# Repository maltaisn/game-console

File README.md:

# Handheld game console

A small six-button handheld game console with a bootloader and games stored in external flash memory.
A complete solution was created to create, simulate, compile and upload apps for the device.

There are currently 2 games written for the console:

- [Tetris](sw/app/tetris)
- [Tile World](sw/app/tworld)

## Specifications

- Display: 1.5" OLED 128x128, 4-bit gray.
- MCU: ATmega3208 @ 10 MHz, 4 kB RAM, 32 kB ROM (bootloader uses 8.25 kB).
- Memory: 4 kB EEPROM (up to 64 kB), 1 MB flash (up to 8 MB).
- Physical: 40 mm x 71 mm x 15.4 mm, 60 g.
- Battery: 850 mAh Li-Po, 5-20h active, several months standby, USB micro B charging.

### Hardware

- MCU: ATmega3208, compatible with ATmega4808, AVR128DA28, AVR64DA28, AVR32DA28 (none tested).
- EEPROM: FT25C32A, 4 kB (compatible with same series devices)
- Flash: AT25SF081B, 1 MB (compatible with 25-series flash devices)
- Display: EastRising ER-OLED015-3 (SSD1327 display controller, 15V VCC)

## Tools and building

Everything was built and tested on Linux only (Ubuntu 20.04).
The PCB was made in KiCAD 6 and the enclosure was made in FreeCAD 0.19.
Building and using the software requires the following tools and libraries:

- AVR GCC >= 5.4.0 (7.3.0 used)
- GCC >= 9
- Python >= 3.7
- freeglut, pulseaudio, libpng

## Architecture

The architecture of the software is described in details in [`sw/README.md`](sw/README.md).

## Project structure

- `hw`: PCB and enclosure
- `sw`: all software SDK including programming utility and all apps.
- `docs`: documentation source files

## License

All code is licensed under Apache License 2.0 and all assets are licensed under
Creative Commons v4.0, unless otherwise indicated.
Bitmap fonts were taken from the [u8g2](https://github.com/olikraus/u8g2/wiki/fntlistall) 
project and are not my work. Credits to my brother for making the game music.

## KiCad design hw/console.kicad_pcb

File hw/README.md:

# Game console hardware

## PCB

The PCB was designed in KiCAD 6.
Two revisions were made, but only the first revision was manufactured
since it was already working with minor changes.

### Revisions

#### Revision 2021A

- Initial revision.

#### Revision 2022A

- Added pull downs on the H-bridge.
- Removed power monitor (was originally meant to monitor shut off and alert the MCU to do last 
    minute operations, but there isn't anywhere near enough on-board capacity to have time to do so).
- Removed low power reset monitor on the MCU, it caused reset when disconnecting
  the USB cable due to momentary drop on 2.8V power rail (not properly decoupled, battery has protection anyway).
- Changed the battery connector which was too small.

Other notable changes that should be made:

- Battery discharge current reading at ADC to allow better SoC estimation.
- Attempt to reduce high pitch noise (related to either display or 15V boost, 
    may be due to ceramic caps oscillating).
- Increase clearance around buttons for better mechanical integration, or change buttons altogether.
- Remove unused H-bridge to drive speaker (only one side used). Replace bridge pull-downs with pull-ups.
- Replace the debug port with an integrated USB to UART chip.

## Enclosure

The enclosure was designed in FreeCAD and 3D printed in black MJF Nylon.
The design is fine considering this was my first experience with 3D modeling
and considering that it wasn't planned for carefully at the time of designing the
PCB. The button design could have been better, they sometimes get stuck and
don't click, but this is usually not an issue.

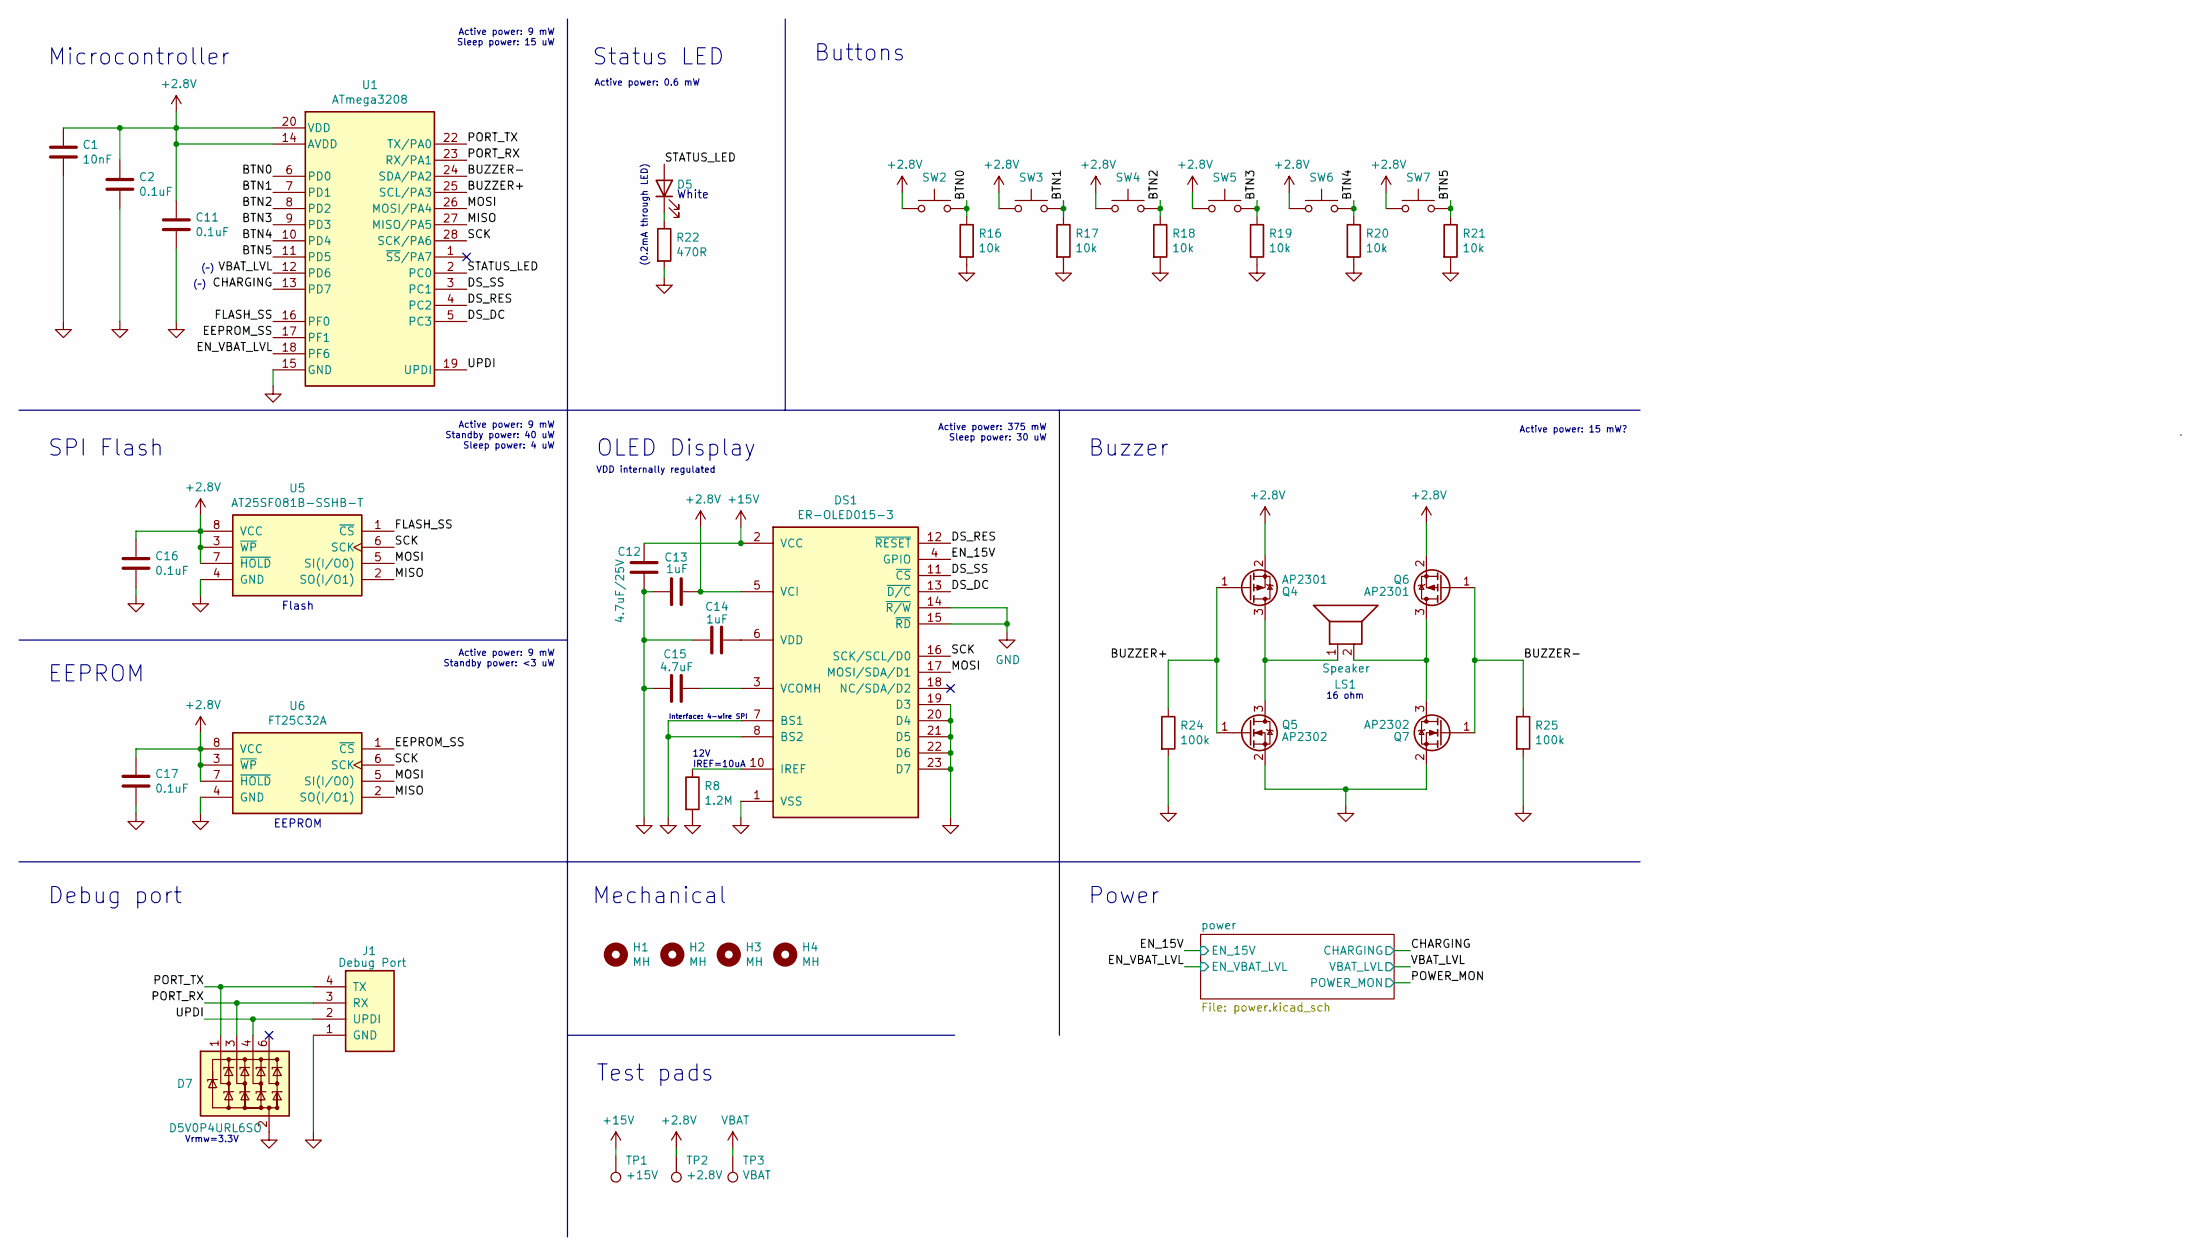
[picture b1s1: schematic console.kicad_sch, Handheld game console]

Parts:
C1: 10nF; C_0603_1608Metric
C2, C11, C16, C17: 0.1uF; C_0603_1608Metric
C12: 4.7uF/25V; C_0603_1608Metric
C13, C14: 1uF; C_0603_1608Metric
C15: 4.7uF; C_0603_1608Metric
D5: LED; D_0805_2012Metric
D7: D5V0P4URL6SO; SOT-23-6
DS1: ER-OLED015-3
H1, H2, H3, H4: MH; MountingHole_2.2mm_M2_ISO7380_Pad
J1: Debug Port; Debug_Port
LS1: Speaker
Q4, Q6: AP2301; SOT-23
Q5, Q7: AP2302; SOT-23
R8: 1.2M; R_0603_1608Metric
R16, R17, R18, R19, R20, R21: 10k; R_0603_1608Metric
R22: 470R; R_0603_1608Metric
R24, R25: 100k; R_0603_1608Metric
SW2, SW3, SW4, SW5, SW6, SW7: SW_Push; SW_SPST_TL3342
TP1: +15V; TestPoint_Pad_D2.0mm
TP2: +2.8V; TestPoint_Pad_D2.0mm
TP3: VBAT; TestPoint_Pad_D2.0mm
U1: ATmega3208; SSOP-28_5.3x10.2mm_P0.65mm
U5: AT25SF081B-SSHB-T; SOIC-8_3.9x4.9mm_P1.27mm
U6: FT25C32A; SO-8_3.9x4.9mm_P1.27mm

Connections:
+2V8: C1.1, C2.1, C11.1, C13.1, C16.1, C17.1, DS1.5 (VCI), Q4.2 (S), Q6.2 (S), SW2.1, SW3.1, SW4.1, SW5.1, SW6.1, SW7.1, TP2.1, U1.14 (AVDD), U1.20 (VDD), U5.3 (~WP), U5.7 (~HOLD), U5.8 (VCC), U6.3 (~WP), U6.7 (~HOLD), U6.8 (VCC); also elsewhere on the board
+15V: C12.1, DS1.2 (VCC), DS1.24 (VCC), TP1.1; also elsewhere on the board
/BTN0: R16.1, SW2.2, U1.6 (PD0)
/BTN1: R17.1, SW3.2, U1.7 (PD1)
/BTN2: R18.1, SW4.2, U1.8 (PD2)
/BTN3: R19.1, SW5.2, U1.9 (PD3)
/BTN4: R20.1, SW6.2, U1.10 (PD4)
/BTN5: R21.1, SW7.2, U1.11 (PD5)
/BUZZER+: Q4.1 (G), Q5.1 (G), R24.1, U1.25 (SCL/PA3)
/BUZZER-: Q6.1 (G), Q7.1 (G), R25.1, U1.24 (SDA/PA2)
/CHARGING: U1.13 (PD7); also elsewhere on the board
/DS_DC: DS1.13 (~D/C), U1.5 (PC3)
/DS_RES: DS1.12 (~RESET), U1.4 (PC2)
/DS_SS: DS1.11 (~CS), U1.3 (PC1)
/EEPROM_SS: U1.17 (PF1), U6.1 (~CS)
/EN_15V: DS1.4 (GPIO); also elsewhere on the board
/EN_VBAT_LVL: U1.18 (PF6); also elsewhere on the board
/FLASH_SS: U1.16 (PF0), U5.1 (~CS)
/MISO: U1.27 (MISO/PA5), U5.2 (SO(I/O1)), U6.2 (SO(I/O1))
/MOSI: DS1.17 (MOSI/SDA/D1), U1.26 (MOSI/PA4), U5.5 (SI(I/O0)), U6.5 (SI(I/O0))
/PORT_RX: D7.3 (K2), J1.3 (RX), U1.23 (RX/PA1)
/PORT_TX: D7.1 (K1), J1.4 (TX), U1.22 (TX/PA0)
/SCK: DS1.16 (SCK/SCL/D0), U1.28 (SCK/PA6), U5.6 (SCK), U6.6 (SCK)
/STATUS_LED: D5.2 (A), U1.2 (PC0)
/UPDI: D7.4 (K3), J1.2 (UPDI), U1.19 (UPDI)
/VBAT_LVL: U1.12 (PD6); also elsewhere on the board
GND: C1.2, C2.2, C11.2, C12.2, C13.2, C14.1, C15.1, C16.2, C17.2, D7.2 (VSS), DS1.1 (VSS), DS1.7 (BS1), DS1.8 (BS2), DS1.9 (VSS), DS1.14 (~R/W), DS1.15 (~RD), DS1.19 (D3), DS1.20 (D4), DS1.21 (D5), DS1.22 (D6), DS1.23 (D7), DS1.25 (VSS), J1.1 (GND), Q5.2 (S), Q7.2 (S), R8.2, R16.2, R17.2, R18.2, R19.2, R20.2, R21.2, R22.2, R24.2, R25.2, U1.15 (GND), U1.21 (GND), U5.4 (GND), U6.4 (GND); also elsewhere on the board
unnamed: C14.2, DS1.6 (VDD)
unnamed: C15.2, DS1.3 (VCOMH)
unnamed: D5.1 (K), R22.1
unnamed: DS1.10 (IREF), R8.1
unnamed: LS1.1, Q4.3 (D), Q5.3 (D)
unnamed: LS1.2, Q6.3 (D), Q7.3 (D)
VBAT: TP3.1; also elsewhere on the board

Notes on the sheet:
SPI Flash
Microcontroller
Debug port
16 ohm
Buttons
Interface: 4-wire SPI
Test pads
Flash
Power
Vrmw=3.3V
Active power: 375 mW Sleep power: 30 uW
(~)
White
Mechanical
IREF=10uA
EEPROM
OLED Display
Active power: 15 mW?
Active power: 9 mW Standby power: <3 uW
Buzzer
Active power: 9 mW Sleep power: 15 uW
Status LED
12V
VDD internally regulated
Active power: 0.6 mW
Active power: 9 mW Standby power: 40 uW Sleep power: 4 uW
(0.2mA through LED)

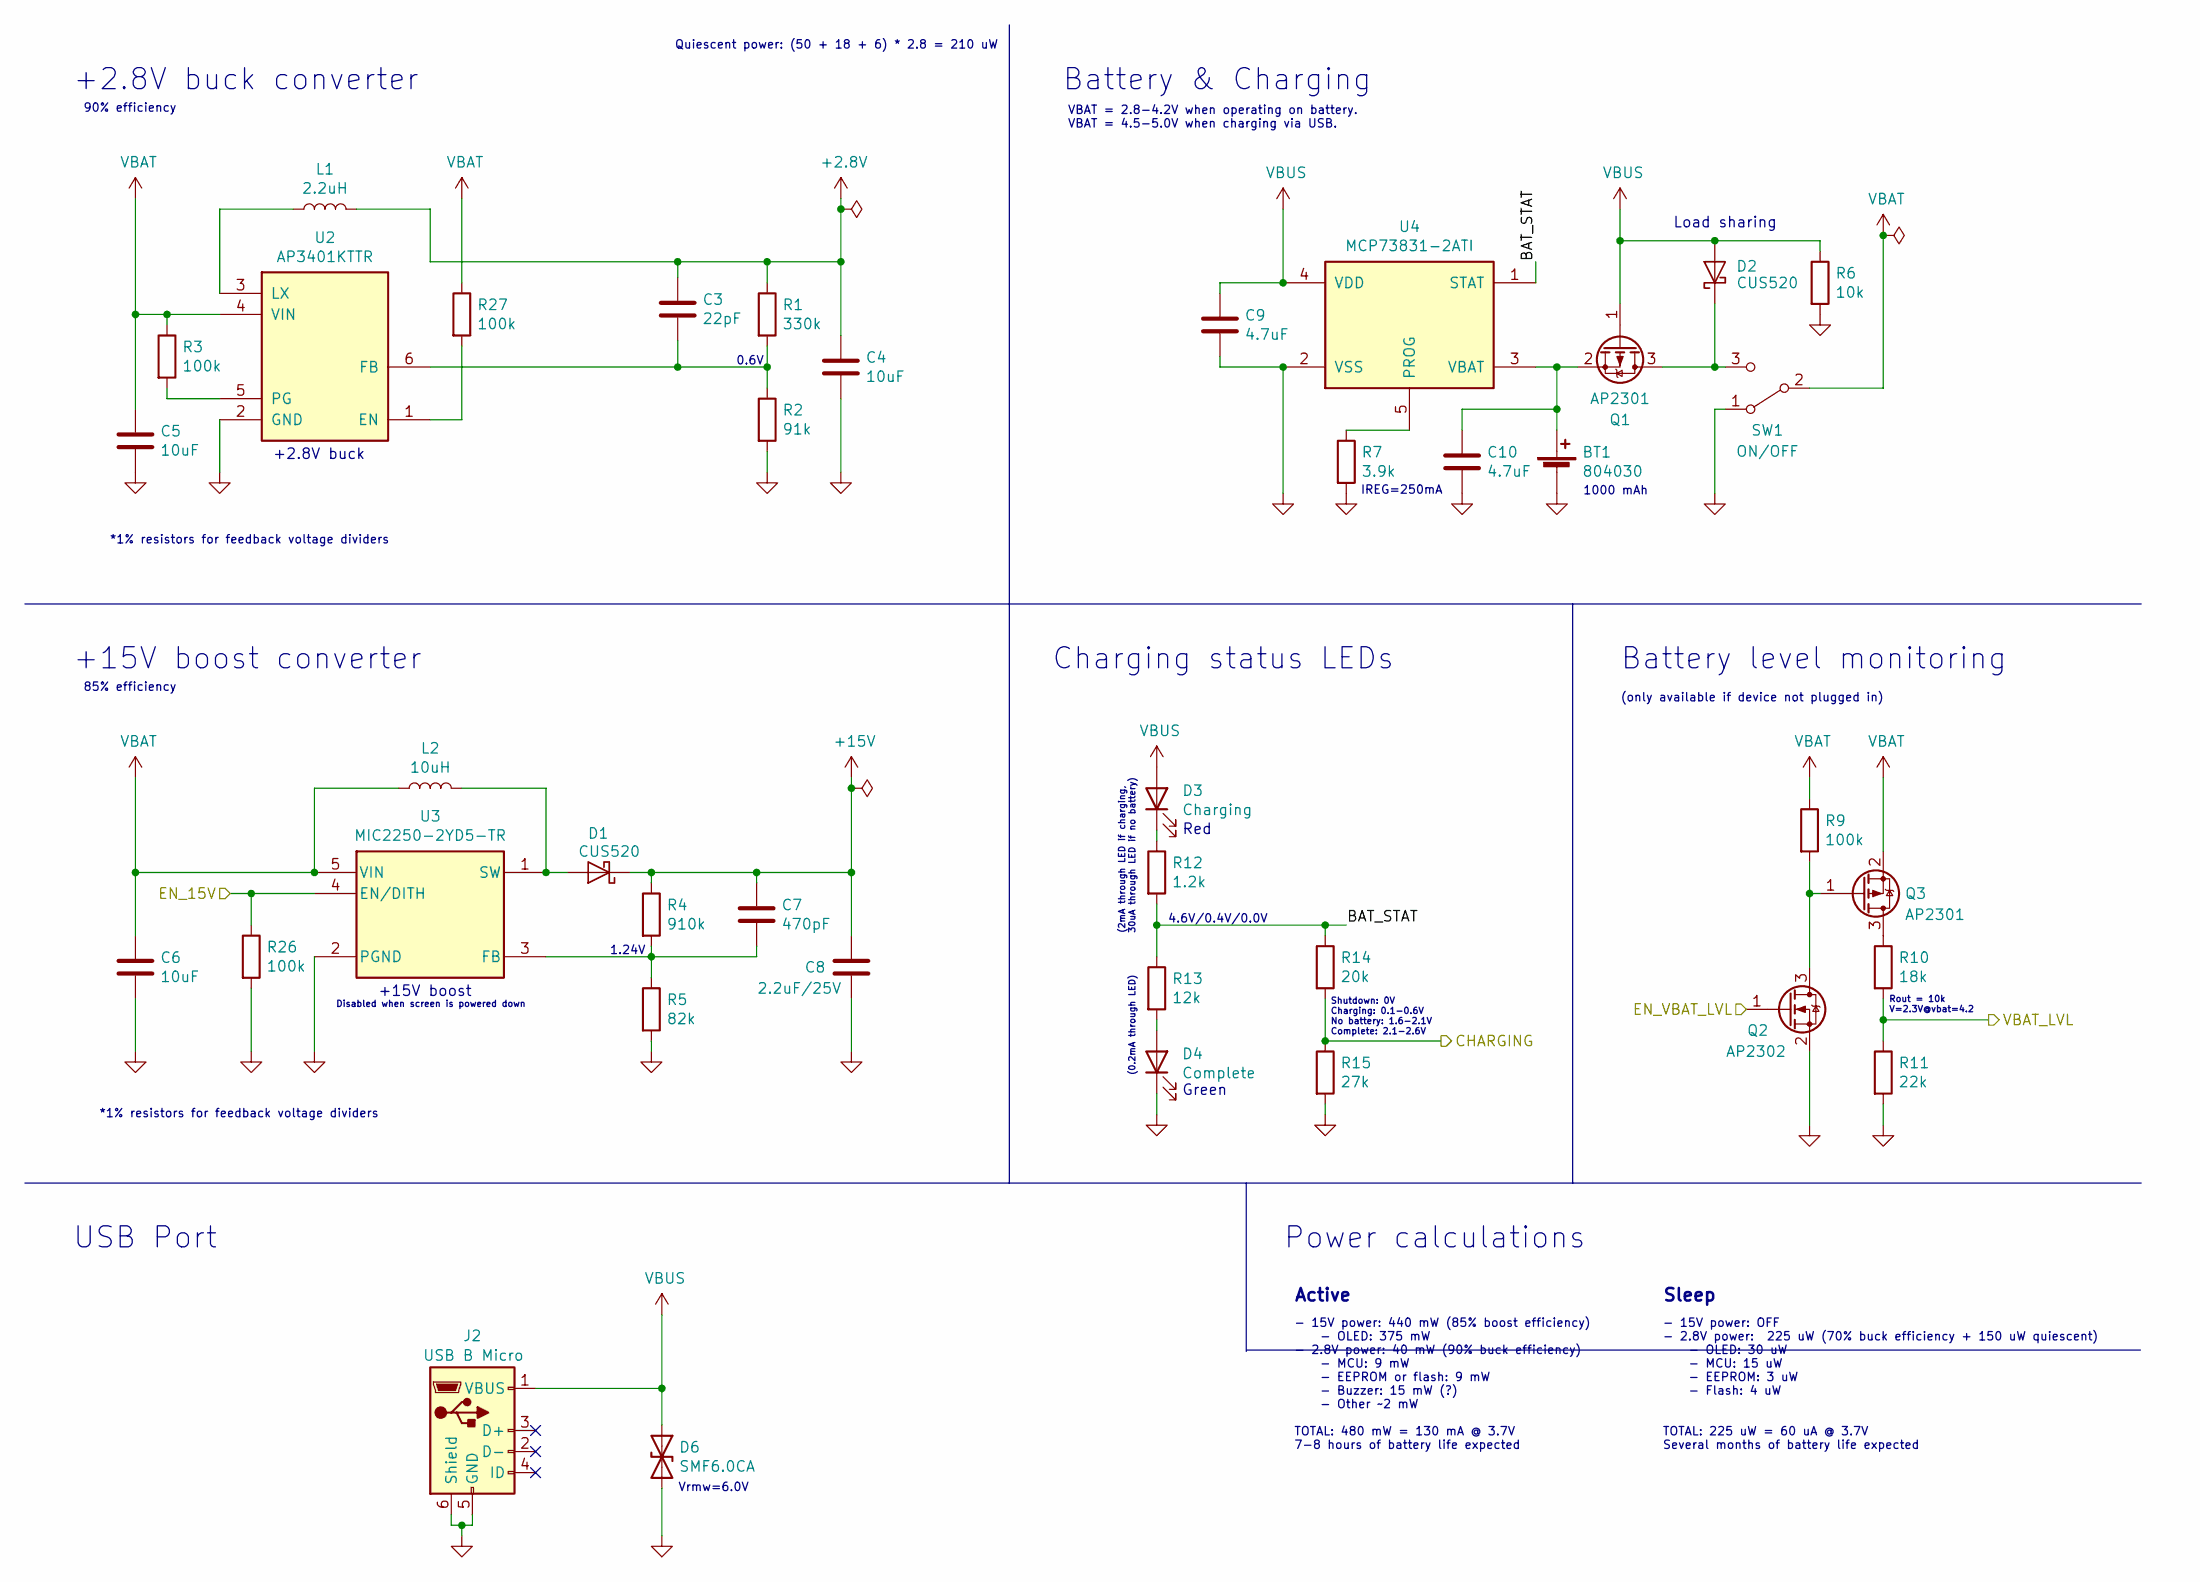
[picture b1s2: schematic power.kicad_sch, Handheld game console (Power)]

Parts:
BT1: 804030; Battery-804030
C3: 22pF; C_0603_1608Metric
C4, C5, C6: 10uF; C_0805_2012Metric
C7: 470pF; C_0603_1608Metric
C8: 2.2uF/25V; C_0603_1608Metric
C9, C10: 4.7uF; C_0603_1608Metric
D1, D2: CUS520; D_SOD-323_HandSoldering
D3: Charging; D_0805_2012Metric
D4: Complete; D_0805_2012Metric
D6: SMF6.0CA; D_SOD-123F
J2: USB B Micro; CUI_UJ2-MIBH-G-SMT-TR
L1: 2.2uH; L_1210_3225Metric
L2: 10uH; L_1210_3225Metric
Q1, Q3: AP2301; SOT-23
Q2: AP2302; SOT-23
R1: 330k; R_0603_1608Metric
R2: 91k; R_0603_1608Metric
R3, R9, R26, R27: 100k; R_0603_1608Metric
R4: 910k; R_0603_1608Metric
R5: 82k; R_0603_1608Metric
R6: 10k; R_0603_1608Metric
R7: 3.9k; R_0603_1608Metric
R10: 18k; R_0603_1608Metric
R11: 22k; R_0603_1608Metric
R12: 1.2k; R_0603_1608Metric
R13: 12k; R_0603_1608Metric
R14: 20k; R_0603_1608Metric
R15: 27k; R_0603_1608Metric
SW1: ON/OFF; 1825232-1
U2: AP3401KTTR; SOT-23-6
U3: MIC2250-2YD5-TR; SOT-23-5
U4: MCP73831-2ATI; SOT-23-5

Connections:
+2V8: C3.1, C4.1, L1.2, R1.1; also elsewhere on the board
+15V: C7.1, C8.1, D1.1 (C), R4.1; also elsewhere on the board
/CHARGING: R14.2, R15.1; also elsewhere on the board
/EN_15V: R26.1, U3.4 (EN/DITH); also elsewhere on the board
/EN_VBAT_LVL: Q2.1 (G); also elsewhere on the board
/VBAT_LVL: R10.2, R11.1; also elsewhere on the board
/power/BAT_STAT: R12.2, R13.1, R14.1, U4.1 (STAT)
GND: BT1.2 (-), C4.2, C5.2, C6.2, C8.2, C9.2, C10.2, D4.1 (K), D6.2 (A2), J2.5 (GND), J2.6 (Shield), Q2.2 (S), R2.2, R5.2, R6.2, R7.2, R11.2, R15.2, R26.2, SW1.1 (A), U2.2 (GND), U3.2 (PGND), U4.2 (VSS); also elsewhere on the board
unnamed: BT1.1 (+), C10.1, Q1.2 (S), U4.3 (VBAT)
unnamed: C3.2, R1.2, R2.1, U2.6 (FB)
unnamed: C7.2, R4.2, R5.1, U3.3 (FB)
unnamed: D1.2 (A), L2.2, U3.1 (SW)
unnamed: D2.1 (C), Q1.3 (D), SW1.3 (C)
unnamed: D3.1 (K), R12.1
unnamed: D4.2 (A), R13.2
unnamed: L1.1, U2.3 (LX)
unnamed: Q2.3 (D), Q3.1 (G), R9.2
unnamed: Q3.3 (D), R10.1
unnamed: R3.2, U2.5 (PG)
unnamed: R7.1, U4.5 (PROG)
unnamed: R27.2, U2.1 (EN)
VBAT: C5.1, C6.1, L2.1, Q3.2 (S), R3.1, R9.1, R27.1, SW1.2 (B), U2.4 (VIN), U3.5 (VIN); also elsewhere on the board
VBUS: C9.1, D2.2 (A), D3.2 (A), D6.1 (A1), J2.1 (VBUS), Q1.1 (G), R6.1, U4.4 (VDD)

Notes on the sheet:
(only available if device not plugged in)
85% efficiency
Red
Sleep
Power calculations
(0.2mA through LED)
Green
Battery & Charging
- 15V power: OFF - 2.8V power: 225 uW (70% buck efficiency + 150 uW quiescent) - OLED: 30 uW - MCU: 15 uW - EEPROM: 3 uW - Flash: 4 uW TOTAL: 225 uW = 60 uA @ 3.7V Several months of battery life expected
90% efficiency
1000 mAh
0.6V
Vrmw=6.0V
1.24V
*1% resistors for feedback voltage dividers
Battery level monitoring
- 15V power: 440 mW (85% boost efficiency) - OLED: 375 mW - 2.8V power: 40 mW (90% buck efficiency) - MCU: 9 mW - EEPROM or flash: 9 mW - Buzzer: 15 mW (?) - Other ~2 mW TOTAL: 480 mW = 130 mA @ 3.7V 7-8 hours of battery life expected
(2mA through LED if charging, 30uA through LED if no battery)
4.6V/0.4V/0.0V
+2.8V buck converter
VBAT = 2.8-4.2V when operating on battery. VBAT = 4.5-5.0V when charging via USB.
Shutdown: 0V Charging: 0.1-0.6V No battery: 1.6-2.1V Complete: 2.1-2.6V
+15V boost converter
Active
USB Port
Rout = 10k V=2.3V@vbat=4.2
Charging status LEDs
Load sharing
+15V boost
Disabled when screen is powered down
IREG=250mA
+2.8V buck
Quiescent power: (50 + 18 + 6) * 2.8 = 210 uW

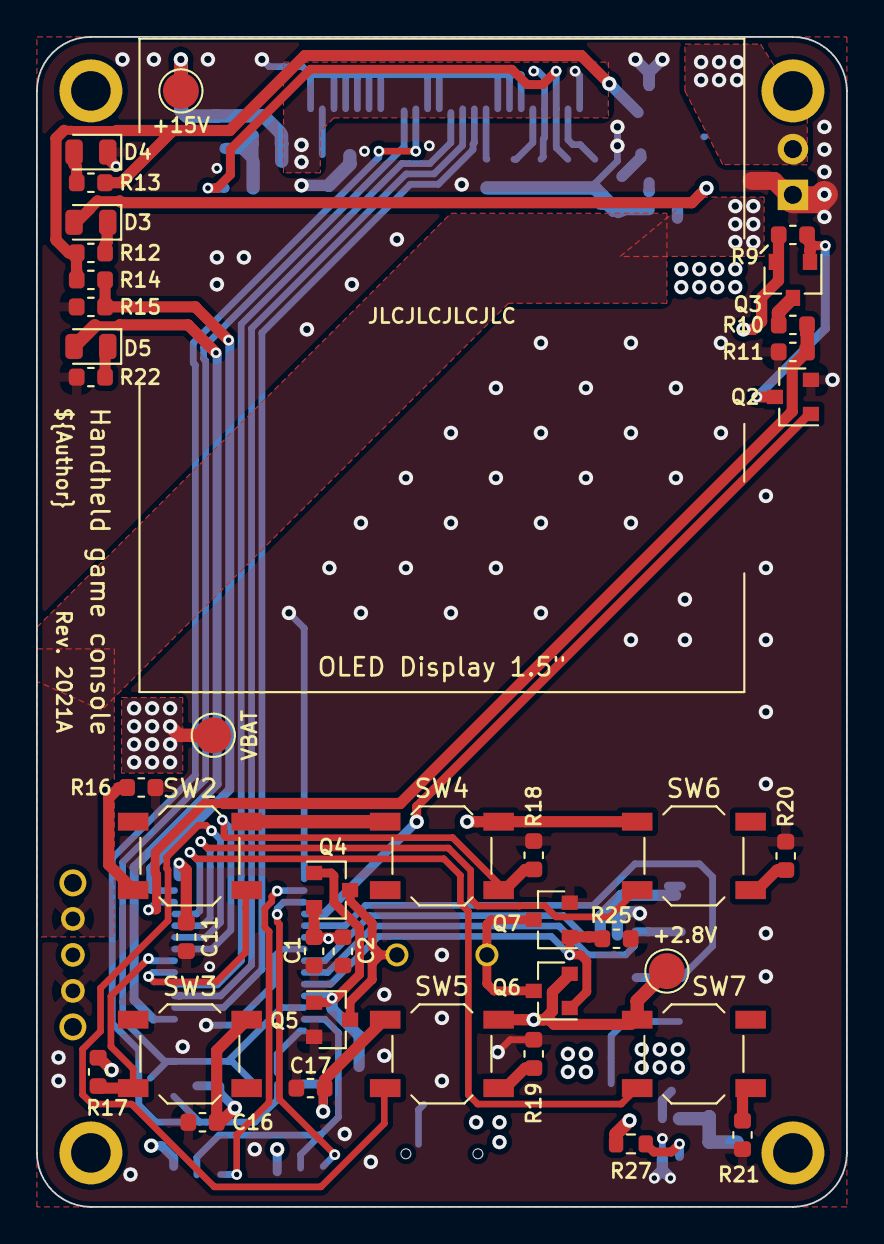
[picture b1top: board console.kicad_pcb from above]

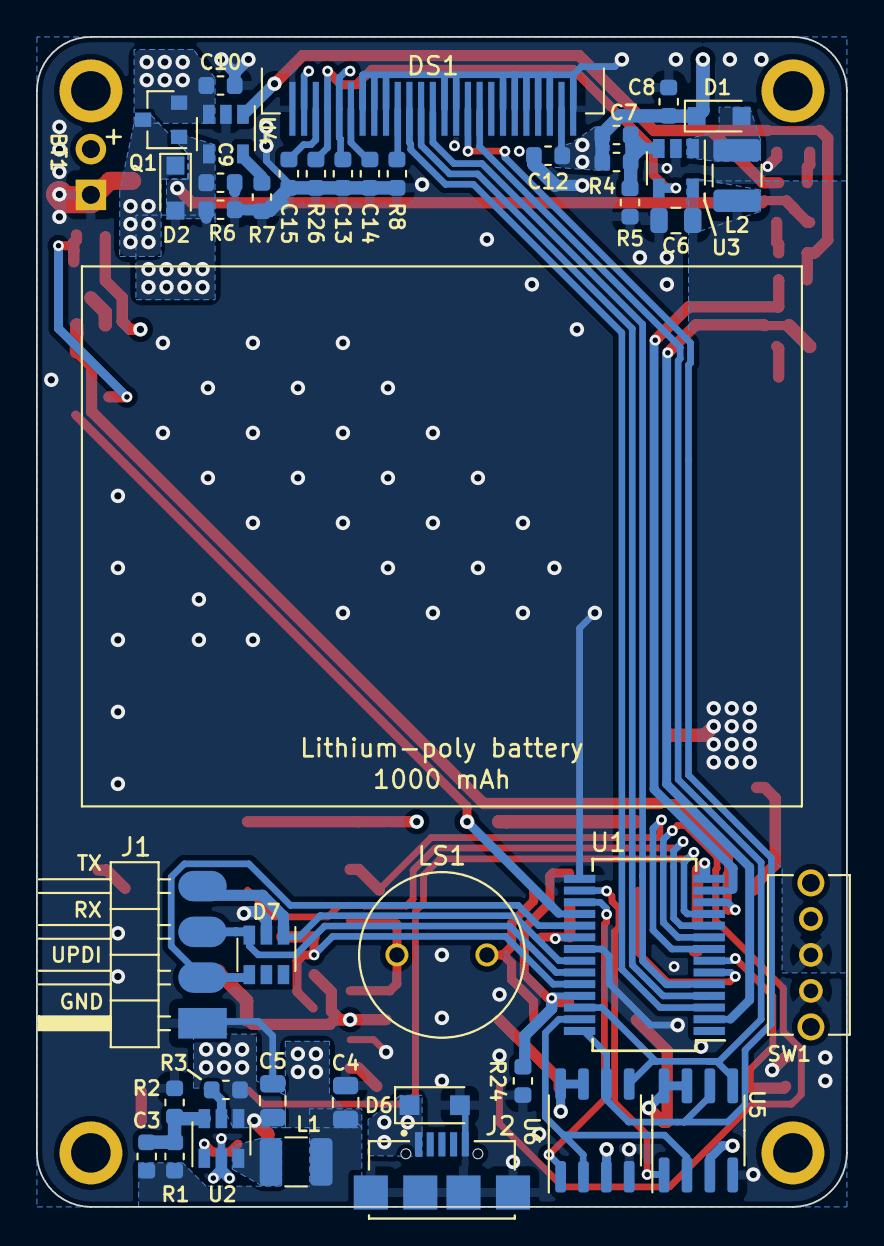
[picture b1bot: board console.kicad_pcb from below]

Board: 4 copper layers, 45.0 x 65.0 mm, 84 parts (40 on the bottom side), 49 nets.

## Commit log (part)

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2021-12-20 Initial commit: hardware
2021-12-22 License & readme
2021-12-22 Move system code to separate folder, power module optimizations
2021-12-22 Automatic battery sampling, battery level buffering, auto shutdown
2021-12-23 Remove option to have no RX/TX buffer
    Not viable!
2021-12-24 Add some const local variables, _WBS
2021-12-24 Add flash driver to gcprog
    Change link baud rate to 500k otherwise reading & writing to flash is painfully slow!
2021-12-27 Add defines for uint24_t
    Will serve later for mock simulator implementation
2021-12-28 Add sound support with 3 channels
    Note: having upload issue, not fully tested.
2021-12-30 Display driver, graphics draw functions, simulated display
    Note: not tested on hardware yet
2021-12-31 Implement graphics line routines, add font/image prototypes
2021-12-31 Performance improvements on graphics_draw_line
2022-01-01 Add text & font to graphics module
    - Fix data module in simulator
    - Add file error guards to eeprom/flash_load_file
2022-01-05 Add 1-bit & 4-bit images to graphics
2022-01-05 Remove .sim file, use two build directories instead
2022-01-06 Code improvements
    - Some const
    - static to indicate length of arrays/buffers
    - Finished implementing sleep
2022-01-06 Add sound generation utility
    Stripped down from buzzer midi project
2022-01-06 Use __builtin_add_overflow for portability
    Program size did not change on AVR target.
2022-01-07 Sleep scheduling and low battery UI
    - Fix glyph not using correct data when font in program memory.
    - Add sleep packet
    - Power down flash before sleep
    - Add built-in graphics font 3x5
    - Add define to disable comms
2022-01-08 Add dialog core module, bug fix
    - Fix graphics_image only drawing the first page due to wrongly placed early exit.
    - Fix font generator giving wrong encoded range info
2022-01-08 Remove unused ellipse/circle graphics prototypes
2022-01-08 Dialog improvements & bug fixes
    - Fix up arrow working from action button in dialog with no items
    - Allow custom result codes for built-in dialog actions.
    - Fix bottom of frame not drawn if title + no buttons
2022-01-10 Add guards to display buffer
    Poor man's valgrind
2022-01-10 Tetris: "how to play" dialog
    - Fix dialog dismiss result not using negative button result if unspecified
2022-01-10 Tetris: render preview pieces & held piece
    - Fix leaderboard dismiss starting game
    - Save options when positive button used
2022-01-10 Tetris: add last clear bonus info
2022-01-10 Add power sleep callbacks
2022-01-11 Tetris: implement leaderboard and high score
2022-01-14 Fix upload bug & many due firmware fixes
    Note: firmware functions hadn't been tested from this commit to 1874ff4a.
    - firmware:
    - Fix unified data interface not working for eeprom & mcu
    - Add protection against dirty resets
    - Set buzzer output high initially (seems to fix a rare reset glitch)
    - Change display driver to do continuous SPI transfers (supported after all, much faster)
2022-01-14 Fix sound corrupting display
    Due to sound track filling its buffer in an interrupt, while SPI transfer for display was in progress.
2022-01-14 Tetris: use primitives instead of images for tiles, flash header check
2022-01-15 Tetris: add music & title screen image
    - Preview volume level in options dialog
    - Add different leaderboard state if shown during game or in main menu.
    - Fix blinking LED on game over not stopped if new game started shortly after.
    - Fix outline for hold piece color constantly changing.
    - Fix leaderboard being written past its end if full.
    - Show version info in title screen.
2022-01-16 Tetris: fix input not ignored on wakeup
    input_get_state_immediate worked, but following input_get_state is debounced and delayed, so it indicated the button as released right after.
2022-01-16 Tetris: add delay between music changes
    - Fix line clear info color changing
2022-01-17 Add missing core assets for sysui
2022-01-17 Linearize grayscale levels on display
    Note: will have to check later which settings minimize power consumption.
2022-01-18 Power module fixes
    - Speaker causes voltage drop on vbus (?), causing failure to detect no battery condition (becomes unknown), so voltage range was widened a bit.
    - Fix enable battery voltage pin not set as output, which caused intermittent failure to read battery level (surprising it worked at all...)
    - Refactor ADC interrupt code a little, removed useless battery percent cache flag.
2022-01-23 Tetris: add sound effects
2022-01-23 Fix channel volume simulator implementation
2022-01-30 Fix cases where display buffer size created short last page
    - Make display_page_yend inclusive
    - Fix implementation issues with different last page height
    - Fix incorrect line spacing runtime check in graphics_set_font
    - Allow changing page height at runtime in simulator
    - Fix headless simulator not initialized in graphics_test
    From here the strategy when making new games is to allocate all leftover RAM to the display buffer, even if it results in weird page heights, like 37, a larger page height will always be faster.
2022-01-31 Add missing reference data for graphics tests
2022-01-31 Reduce branching and provide fast path for RLE sequence in mixed 4-bit image decoder
    For tiger128.png: 148 ms (77cyc/px) -> 134 ms (68cyc/px)
    Optimizing only the function with -O3 gives 121 ms but +270 bytes.
2022-01-31 Change indexing for raw images: implicit index
    - Raw image layout is predictable hence index is useless. Seeking to the first row is possible trivially, provided that the encoder state is reset on each row.
    - Few swap optimizations (a color always has high nibble = 0).
2022-02-05 Add linker script to optimize RAM usage
    - Add section to share RAM with display buffer, for temporary data (wouldn't have been a problem with a heap!).
    - Add script to better calculate section size (other methods have some shortcomings)
    - Put some static variables in noinit section (not much of an optimization, more self documentation actually)
    - Fix display state not reset on display reset.
2022-02-26 Tetris: bug fixes & improvements
    - Increase block constrast (some blocks were really hard too see on gc), and update title screen image accordingly
    - Add access to general options from pause dialog.
    core/sys bugs:
    - Fix sound_start and sound_stop not stoppping or
    starting notes on affected channels.
    - Fix buffer underflow in dialog text field if all blank.
2022-03-06 Tetris: increase tempo with level
2022-04-24 PCB: removed reset monitor
    Causes drop in power when USB is disconnected and not really necessary.
2022-05-23 System app
    - Add defines in dialog to disable features to lower code size.
    - Add define to use EEPROM in absolute mode (for bootloader and system app)
    - Fix include leaking system API in several places
    - Fix boot version not read correctly due to make lazy initialization
    - Remove all pthread uses, wasn't really needed.
2022-05-28 SPI device emulation and various fixes
    - Flash and EEPROM are not entirely in the core library, same code runs in simulation.
    - Add --sim mode to gcprog as a UART client to the simulator
    - Abstraction over external memory simulation functions.
    - Fix wrong load address for shared data section
    - Fix unable to read whole memory in raw access mode in gcprog
    - Fix broken test target with previous changes to Makefiles
2022-05-28 Update graphics image tests (remove horizontal region)
    - Fix image encoder not checking max dimensions
    - Add runtime check for image x bounds.
    - Fix color byte not reset on row boundary when encoding 1-bit raw images
    - Auto fix path when running standalone encode utilities.
2022-06-03 Several fixes: bootloader now working on hardware
    Bootloader:
    - Select last loaded app by default.
    - Prevent signature of some BOOTLOADER_NOINLINE functions changing due to constant propagation.
    - Remove lock on oscillator calibration registers preventing clock calibration, see errata.
    - Program fuses with the HEX file instead of manually.
    - Fix wrong protected write type used for enabling SPM.
2022-06-04 Include subsection usage in avr_size.py
2022-06-04 System app fixes
    - Fix battery voltage shown when not discharging.
    - Fix relative flash read used to read app name and author.
2022-06-12 Fix concurrency issue with simulated flash and eeprom.
2022-06-14 Documentation
2022-06-17 TWorld: level pack selection
    - Asset packer fixes:
    - Fix missing array when last packed object belongs in an array.
    - Fix missing array when consecutive objects form different arrays.
    - Fix underscore not allowed in group name.
2022-06-19 TWorld: utility functions
2022-06-22 TWorld: implement password use
2022-06-23 TWorld: fixes after first hardware test
    - Fix wrong frame delay comparison causing low FPS.
    - Fix missing cast in LZSS 2 bytes backref decoding.
    - Fix level pack rendering showing one extra pack when less than 4 packs.
    Core library:
    - Fix annoying clang-tidy warning asking to use lround in millis_to_ticks.
    - Add FPS monitor utility.
2022-06-24 TWorld: show time left with inventory, low time counter
    - Track time left instead of current time.
    - Hide inventory when pause dialog is shown.
    - Fix unlocked packs cleared by saving options.
2022-06-25 TWorld: show hint
    - Add separator game states for better maintainability.
    - Fix bottom navigation arrow wrong color if less items than can be shown in a single screen.
2022-06-26 TWorld: level music
    Reused same music controller as tetris, some features may be removed later.
2022-06-29 TWorld: main menu music
2022-06-29 TWorld: level fail dialog message
    - Add option for top margin in dialog module.
    - Small optimization in dialog_init.
    - Fix fading pattern appearing wrong with 16 colors only in main menu image
    - Add string builder in assets packer.
    - Distinguish between block and monster collision.
2022-07-01 TWorld: level tests, level pack unlocking
    - Add automatic level tests for all levels in all packs.
    - Unlock level packs if previous has a certain completion ratio.
    - Fix cloner copying actor index of parent to clone.
    - Fix misplaced return in teleport_actor.
    - Fix wrong THIN_WALL_DIR_TO mask.
    - Fix blob PRNG used for tests.
2022-07-01 Tworld: animated bottom tiles
2022-07-02 Bootloader & core library fixes
    - Fix CRC check failing when code size is multiple of page size.
    - Fix boot symbols filter not excluding some unwanted symbols.
    - Misc fixes to remove warnings on avr-gcc 12 (but avr-gcc 12 not working yet...)
    - Fix sleep countdown not working in simulator.
2022-07-03 TWorld: swimming, burned & drowned chip tiles
    - Fix wrong state delay on fail/complete.
2022-07-08 TWorld: bug fix
    - Fix diagonal input resolution not using last chip direction but sometimes forced direction.
    - More efficient tile macros, re-encoded static bottom tiles.
2022-07-09 TWorld: python implementation
2022-07-10 System app simulation bug fix
    - Fix structs not packed causing manual memory address calculation to be misaligned.
2022-07-22 TWorld: bug fixes
    - Fix type 1 collision not occuring when chip overrides force move
    - Fix unslide working in some cases on ice (and maybe teleporter)
    - Change tests to show blacklisted tests as skipped instead of hiding them completely.
2022-07-22 TWorld: more sound effects (boot, last chip) and level end music change
    - Also play level end music if music disabled but sound effects enabled.
2022-07-23 TWorld: minor bug fixes
    - Fix actor not appearing on top of chip after death if dying straight out of cloner.
    - Fix end music only played when first dying.
2022-08-08 Minor documentation fixes, simulator captures zoom
2022-09-11 TWorld: remove black (0) from most tiles
    Note: it doesn't seem to help at all, but whatever. In theory black (0) involves no 1st precharge on the OLED so it might have cause issues for pixels further on the scanline but turns out it isn't t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
    - Made ice texture slightly lighter
    - Update menu and cover images

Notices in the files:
parts and their libraries:
Copyright 2021 Accelerated Designs. All rights reserved.
